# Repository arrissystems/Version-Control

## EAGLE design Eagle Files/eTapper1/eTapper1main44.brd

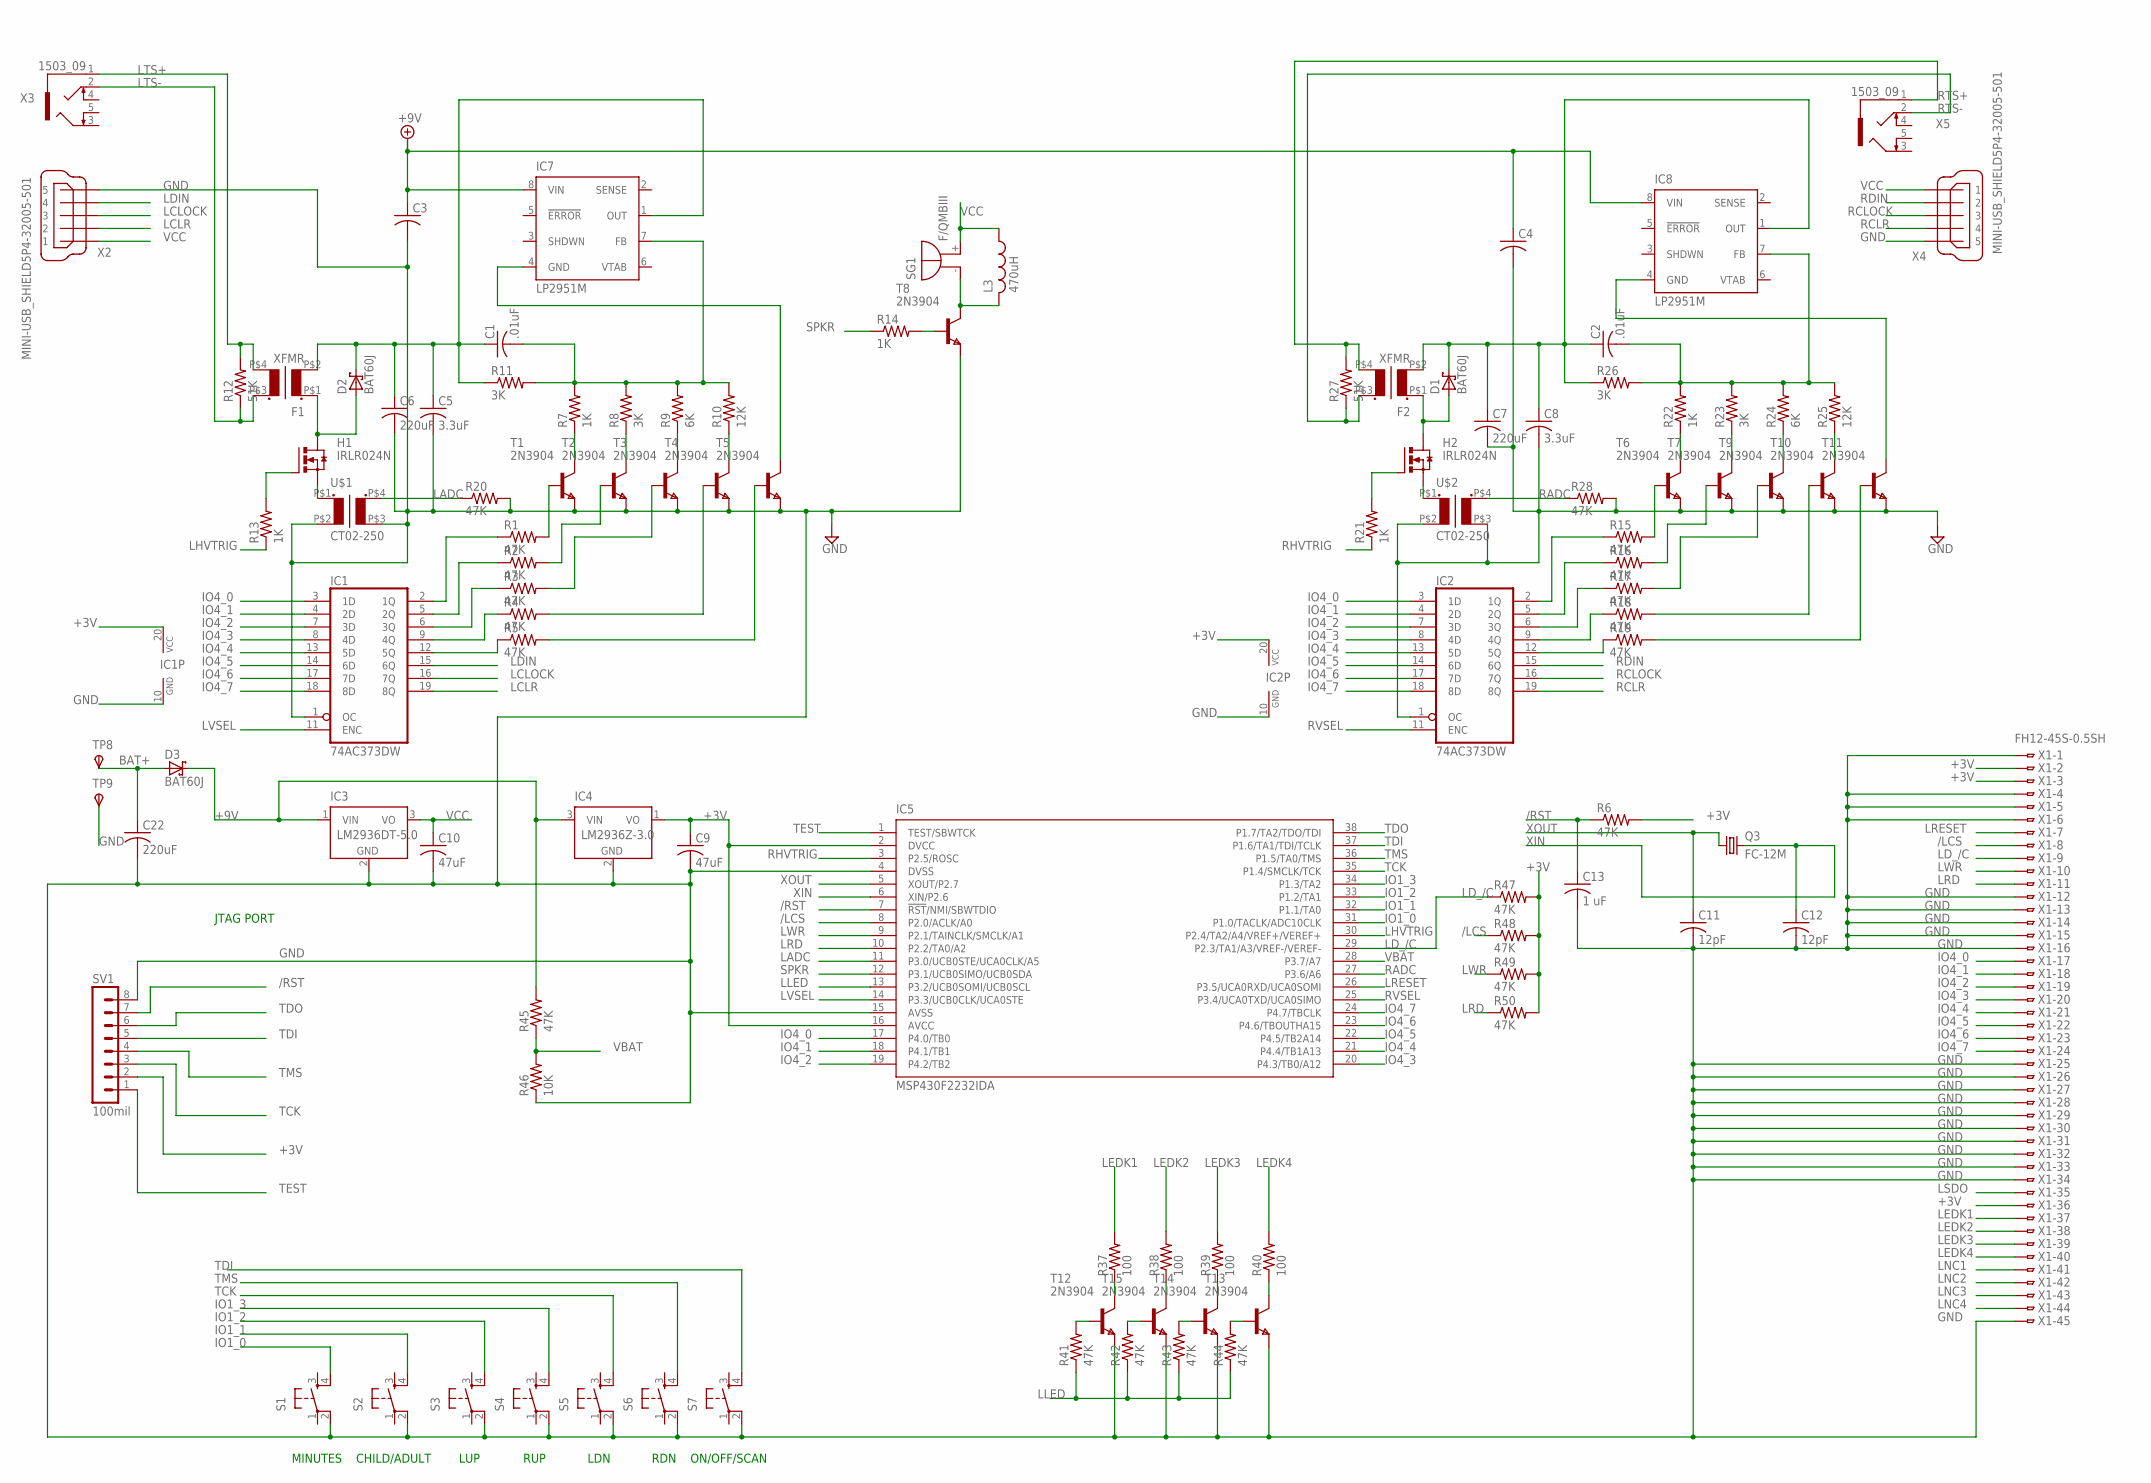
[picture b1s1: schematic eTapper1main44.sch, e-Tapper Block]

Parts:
C1, C2: .01uF; C0805
C3, C4: C-USC1206; C1206
C5, C8: 3.3uF; C0805
C6, C7, C22: 220uF; C1206
C9, C10: 47uF; C1206
C11, C12: 12pF; C0805
C13: 1 uF; C0805
D1, D2, D3: BAT60J; SOD323_ST
F1, F2: XFMR
H1, H2: IRLR024N; D-PAK_TO252AA
IC1, IC2: 74AC373DW; SO20W
IC3: LM2936DT-5.0; TO252
IC4: LM2936Z-3.0; TO92
IC5: MSP430F2232IDA; TSSOP38_R-PDSO-G38-DA
IC7, IC8: LP2951M; SO08
L3: 470uH; L2825P
Q3: FC-12M
R1, R2, R3, R4, R5, R6, R15, R16, R17, R18, R19, R20, R28, R41, R42, R43, R44, R45, R47, R48, R49, R50: 47K; R0402
R7, R13, R14, R21, R22: 1K; R0402
R8, R11, R23, R26: 3K; R0402
R9, R24: 6K; R0402
R10, R25: 12K; R0402
R12, R27: 51K; R0402
R37, R38, R39, R40: 100; R0402
R46: 10K; R0402
S1, S2, S3, S4, S5, S6, S7: 10-XX; B3F-10XX
SG1: F/QMBIII
SV1: 100mil; MA08-1
T1, T2, T3, T4, T5, T6, T7, T8, T9, T10, T11, T12, T13, T14, T15: 2N3904; SOT-23
TP8, TP9: TPSPAD1-20; P1-20
U$1, U$2: CT02-250
X1: FH12-45S-0.5SH
X2, X4: MINI-USB_SHIELD5P4-32005-501; 32005-501
X3, X5: 1503_09

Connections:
+3V: C9.1, IC1.20 (VCC), IC2.20 (VCC), IC4.1 (VO), IC5.2 (DVCC), IC5.16 (AVCC), R6.2, R47.2, R48.2, R49.2, R50.2, SV1.2, X1.2, X1.3, X1.36
+9V: C3.1, C4.1, D3.C, IC3.1 (VIN), IC4.3 (VIN), IC7.8 (VIN), IC8.8 (VIN), R45.2
/LCS: IC5.8 (P2.0/ACLK/A0), R48.1, X1.8
/RST: C13.1, IC5.7 (!RST!/NMI/SBWTDIO), R6.1, SV1.7
BAT+: C22.1, D3.A, TP8.TP
GND: C3.2, C4.2, C5.2, C6.2, C7.2, C8.2, C9.2, C10.2, C11.2, C12.2, C13.2, C22.2, IC1.1 (OC), IC1.10 (GND), IC2.1 (OC), IC2.10 (GND), IC3.2 (GND), IC4.2 (GND), IC5.4 (DVSS), IC5.15 (AVSS), R20.2, R28.2, R46.1, S1.2 (P1), S2.2 (P1), S3.2 (P1), S4.2 (P1), S5.2 (P1), S6.2 (P1), S7.2 (P1), SV1.8, T1.2 (E), T2.2 (E), T3.2 (E), T4.2 (E), T5.2 (E), T6.2 (E), T7.2 (E), T8.2 (E), T9.2 (E), T10.2 (E), T11.2 (E), T12.2 (E), T13.2 (E), T14.2 (E), T15.2 (E), TP9.TP, U$1.P$2 (P2), U$1.P$3 (S2), U$2.P$2 (P2), U$2.P$3 (S2), X1.1, X1.4, X1.5, X1.6, X1.12, X1.13, X1.14, X1.15, X1.16, X1.25, X1.26, X1.27, X1.28, X1.29, X1.30, X1.31, X1.32, X1.33, X1.34, X1.45, X2.5, X4.5
IO1_0: IC5.31 (P1.0/TACLK/ADC10CLK), S1.4 (S1)
IO1_1: IC5.32 (P1.1/TA0), S2.4 (S1)
IO1_2: IC5.33 (P1.2/TA1), S3.4 (S1)
IO1_3: IC5.34 (P1.3/TA2), S4.4 (S1)
IO4_0: IC1.3 (1D), IC2.3 (1D), IC5.17 (P4.0/TB0), X1.17
IO4_1: IC1.4 (2D), IC2.4 (2D), IC5.18 (P4.1/TB1), X1.18
IO4_2: IC1.7 (3D), IC2.7 (3D), IC5.19 (P4.2/TB2), X1.19
IO4_3: IC1.8 (4D), IC2.8 (4D), IC5.20 (P4.3/TB0/A12), X1.20
IO4_4: IC1.13 (5D), IC2.13 (5D), IC5.21 (P4.4/TB1A13), X1.21
IO4_5: IC1.14 (6D), IC2.14 (6D), IC5.22 (P4.5/TB2A14), X1.22
IO4_6: IC1.17 (7D), IC2.17 (7D), IC5.23 (P4.6/TBOUTHA15), X1.23
IO4_7: IC1.18 (8D), IC2.18 (8D), IC5.24 (P4.7/TBCLK), X1.24
LADC: IC5.11 (P3.0/UCB0STE/UCA0CLK/A5), R20.1, U$1.P$4 (S1)
LCLOCK: IC1.16 (7Q), X2.3
LCLR: IC1.19 (8Q), X2.2
LDIN: IC1.15 (6Q), X2.4
LD_/C: IC5.29 (P2.3/TA1/A3/VREF-/VEREF-), R47.1, X1.9
LEDK1: R37.2, X1.37
LEDK2: R38.2, X1.38
LEDK3: R39.2, X1.39
LEDK4: R40.2, X1.40
LHVTRIG: IC5.30 (P2.4/TA2/A4/VREF+/VEREF+), R13.1
LLED: IC5.13 (P3.2/UCB0SOMI/UCB0SCL), R41.1, R42.1, R43.1, R44.1
LNC1: X1.41
LNC2: X1.42
LNC3: X1.43
LNC4: X1.44
LRD: IC5.10 (P2.2/TA0/A2), R50.1, X1.11
LRESET: IC5.26 (P3.5/UCA0RXD/UCA0SOMI), X1.7
LSDO: X1.35
LTS+: F1.P$4 (S2), R12.2, X3.1
LTS-: F1.P$3 (S1), R12.1, X3.2
LVSEL: IC1.11 (ENC), IC5.14 (P3.3/UCB0CLK/UCA0STE)
LWR: IC5.9 (P2.1/TAINCLK/SMCLK/A1), R49.1, X1.10
unnamed: IC1.2 (1Q), R1.1
unnamed: IC1.5 (2Q), R2.1
unnamed: IC1.6 (3Q), R3.1
unnamed: IC1.9 (4Q), R4.1
unnamed: IC1.12 (5Q), R5.1
unnamed: L3.2, SG1.- (+), T8.1 (C)
unnamed: R4.2, T4.3 (B)
unnamed: R5.2, T5.3 (B)
unnamed: D2.A, F1.P$1 (P1), H1.4 (D)
unnamed: R7.1, T1.1 (C)
unnamed: R8.1, T2.1 (C)
unnamed: R9.1, T3.1 (C)
unnamed: R1.2, T1.3 (B)
unnamed: R2.2, T2.3 (B)
unnamed: R3.2, T3.3 (B)
unnamed: R10.1, T4.1 (C)
unnamed: C1.2, IC7.7 (FB), R7.2, R8.2, R9.2, R10.2, R11.2
unnamed: C1.1, C5.1, C6.1, D2.C, F1.P$2 (P2), IC7.1 (OUT), R11.1
unnamed: D1.A, F2.P$1 (P1), H2.4 (D)
unnamed: IC2.2 (1Q), R15.1
unnamed: H1.1 (G), R13.2
unnamed: R14.2, T8.3 (B)
unnamed: H1.3 (S), U$1.P$1 (P1)
unnamed: IC2.5 (2Q), R16.1
unnamed: IC2.6 (3Q), R17.1
unnamed: IC2.9 (4Q), R18.1
unnamed: IC2.12 (5Q), R19.1
unnamed: R44.2, T13.3 (B)
unnamed: R15.2, T6.3 (B)
unnamed: R16.2, T7.3 (B)
unnamed: R17.2, T9.3 (B)
unnamed: R18.2, T10.3 (B)
unnamed: R19.2, T11.3 (B)
unnamed: R22.1, T6.1 (C)
unnamed: R23.1, T7.1 (C)
unnamed: R24.1, T9.1 (C)
unnamed: R25.1, T10.1 (C)
unnamed: C2.2, IC8.7 (FB), R22.2, R23.2, R24.2, R25.2, R26.2
unnamed: C2.1, C7.1, C8.1, D1.C, F2.P$2 (P2), IC8.1 (OUT), R26.1
unnamed: R37.1, T12.1 (C)
unnamed: H2.1 (G), R21.2
unnamed: R38.1, T15.1 (C)
unnamed: R39.1, T14.1 (C)
unnamed: IC7.4 (GND), T5.1 (C)
unnamed: R40.1, T13.1 (C)
unnamed: IC8.4 (GND), T11.1 (C)
unnamed: R43.2, T14.3 (B)
unnamed: R41.2, T12.3 (B)
unnamed: R42.2, T15.3 (B)
unnamed: H2.3 (S), U$2.P$1 (P1)
RADC: IC5.27 (P3.6/A6), R28.1, U$2.P$4 (S1)
RCLOCK: IC2.16 (7Q), X4.3
RCLR: IC2.19 (8Q), X4.4
RDIN: IC2.15 (6Q), X4.2
RHVTRIG: IC5.3 (P2.5/ROSC), R21.1
RTS+: F2.P$4 (S2), R27.2, X5.1
RTS-: F2.P$3 (S1), R27.1, X5.2
RVSEL: IC2.11 (ENC), IC5.25 (P3.4/UCA0TXD/UCA0SIMO)
SPKR: IC5.12 (P3.1/UCB0SIMO/UCB0SDA), R14.1
TCK: IC5.35 (P1.4/SMCLK/TCK), S5.4 (S1), SV1.3
TDI: IC5.37 (P1.6/TA1/TDI/TCLK), S7.4 (S1), SV1.5
TDO: IC5.38 (P1.7/TA2/TDO/TDI), SV1.6
TEST: IC5.1 (TEST/SBWTCK), SV1.1
TMS: IC5.36 (P1.5/TA0/TMS), S6.4 (S1), SV1.4
VBAT: IC5.28 (P3.7/A7), R45.1, R46.2
VCC: C10.1, IC3.3 (VO), L3.1, SG1.+ (-), X2.1, X4.1
XIN: C12.1, IC5.6 (XIN/P2.6), Q3.2
XOUT: C11.1, IC5.5 (XOUT/P2.7), Q3.1

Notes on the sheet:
ON/OFF/SCAN
MINUTES
CHILD/ADULT
LUP
RUP
JTAG PORT
LDN
RDN

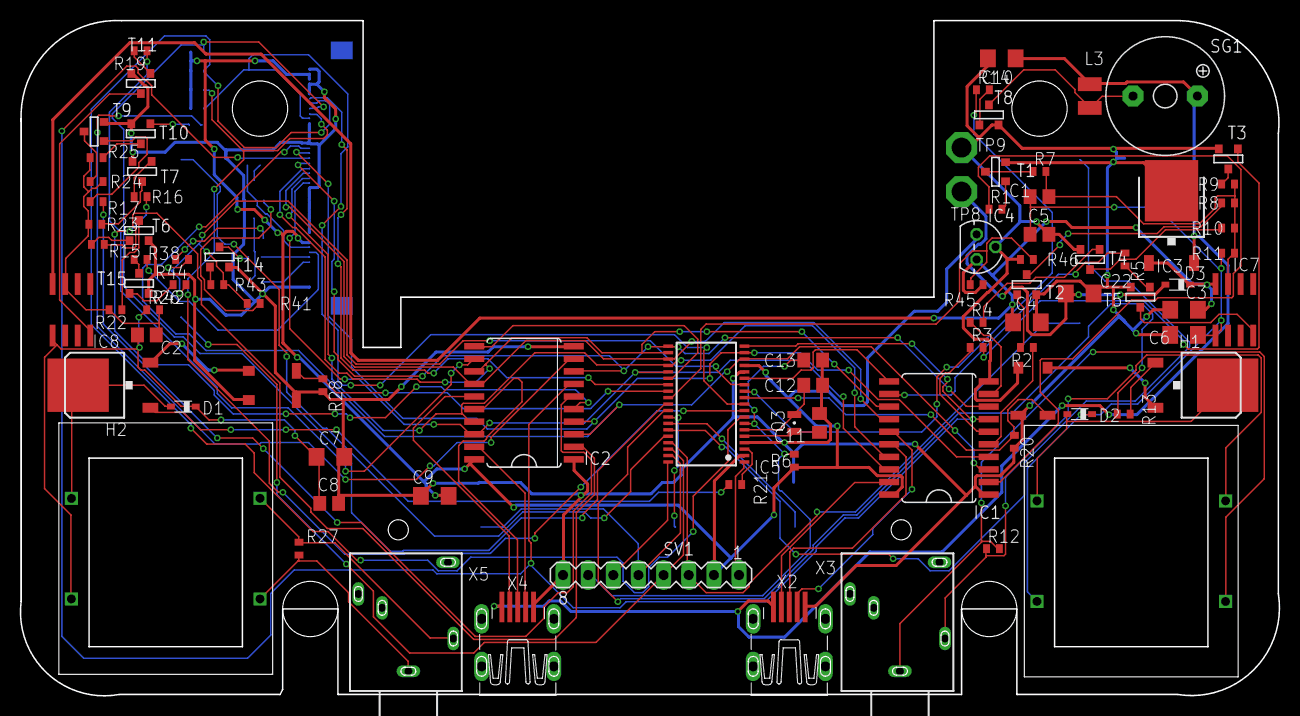
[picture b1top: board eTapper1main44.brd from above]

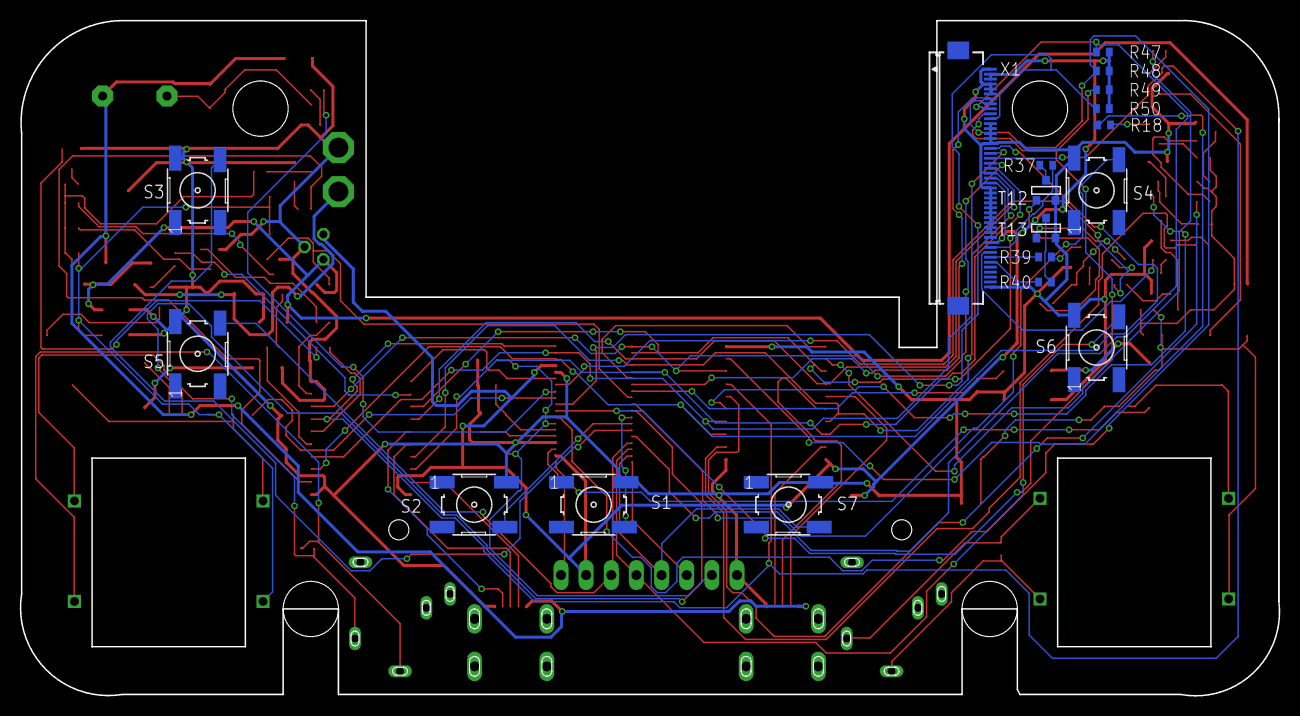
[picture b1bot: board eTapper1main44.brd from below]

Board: 2 copper layers, 127.2 x 68.2 mm, 105 parts (18 on the bottom side), 103 nets.

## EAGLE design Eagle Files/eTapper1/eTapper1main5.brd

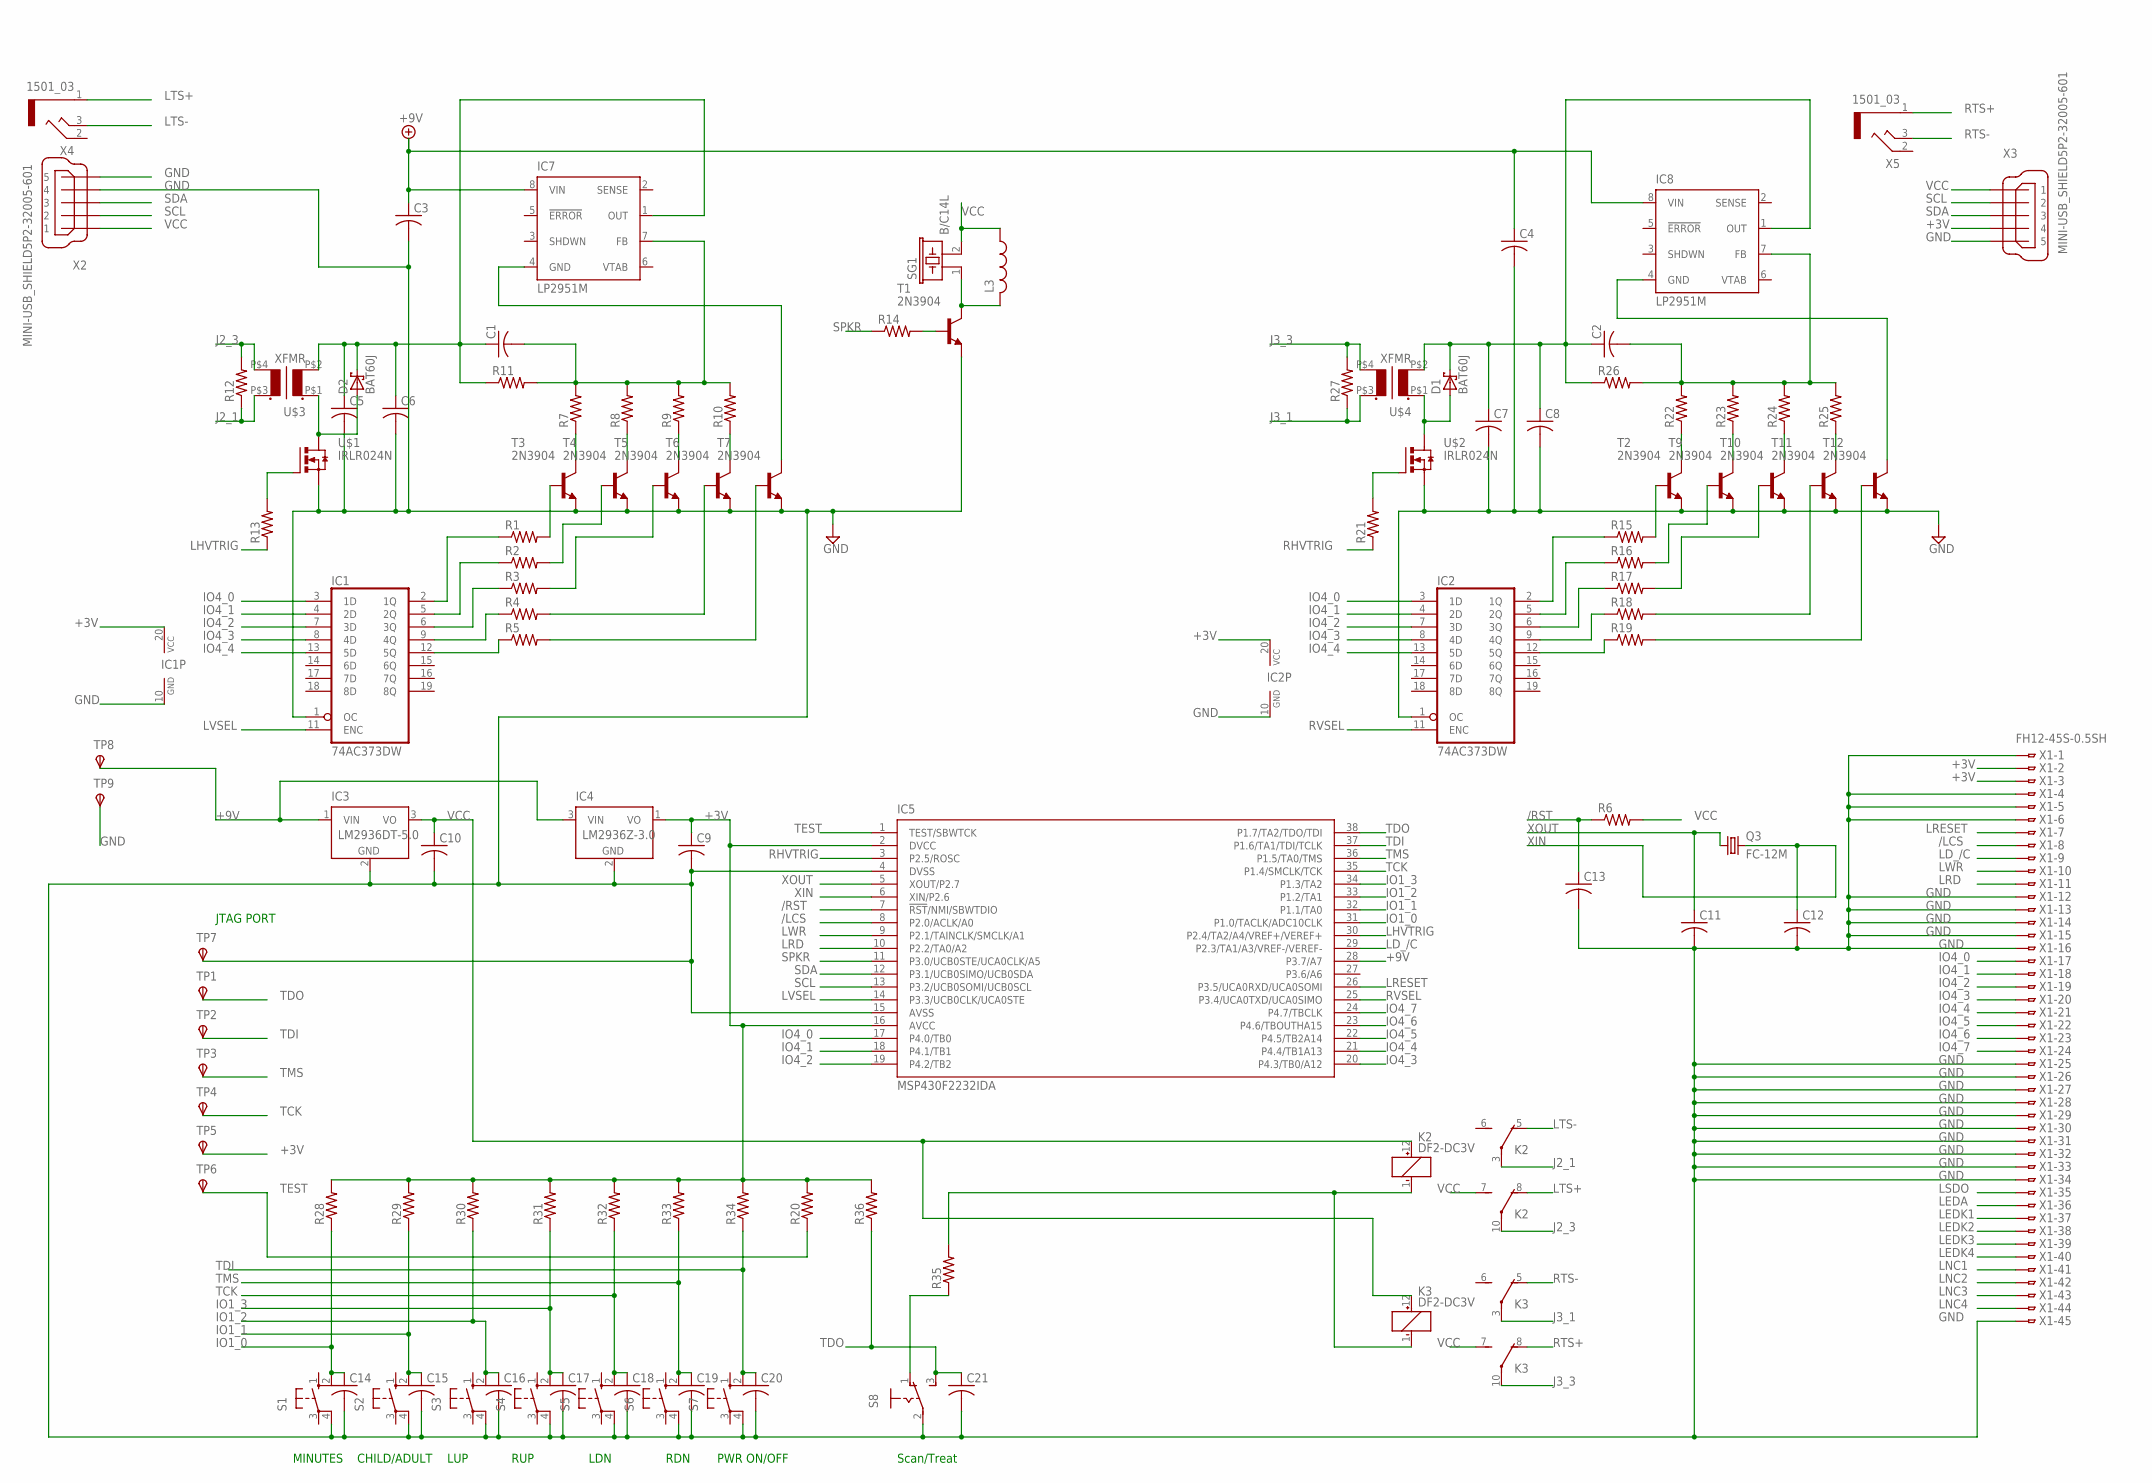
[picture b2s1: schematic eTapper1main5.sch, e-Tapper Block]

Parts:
C1, C2, C3, C4, C5, C6, C7, C8, C9, C10, C11, C12, C13, C14, C15, C16, C17, C18, C19, C20, C21: C-USC0805; C0805
D1, D2: BAT60J; SOD323_ST
IC1, IC2: 74AC373DW; SO20W
IC3: LM2936DT-5.0; TO252
IC4: LM2936Z-3.0; TO92
IC5: MSP430F2232IDA; TSSOP38_R-PDSO-G38-DA
IC7, IC8: LP2951M; SO08
K2, K3: DF2-DC3V; DF2
L3: L-USL2825P; L2825P
Q3: FC-12M
R1, R2, R3, R4, R5, R6, R7, R8, R9, R10, R11, R12, R13, R14, R15, R16, R17, R18, R19, R20, R21, R22, R23, R24, R25, R26, R27, R28, R29, R30, R31, R32, R33, R34, R35, R36: R-US_R0402; R0402
S1, S2, S3, S4, S5, S6, S7: 10-XX; B3F-10XX
S8: M251
SG1: B/C14L
T1, T2, T3, T4, T5, T6, T7, T9, T10, T11, T12: 2N3904; TO92
TP1, TP2, TP3, TP4, TP5, TP6, TP7, TP8, TP9: TPSTP06R; TP06R
U$1, U$2: IRLR024N; I-PAK_TO251AA
U$3, U$4: XFMR
X1: FH12-45S-0.5SH
X2, X3: MINI-USB_SHIELD5P2-32005-601; 32005-601
X4, X5: 1501_03

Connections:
+3V: C9.1, IC1.20 (VCC), IC2.20 (VCC), IC4.1 (VO), IC5.2 (DVCC), IC5.16 (AVCC), R20.2, R28.2, R29.2, R30.2, R31.2, R32.2, R33.2, R34.2, R36.2, TP5.TP, X1.2, X1.3, X3.4
+9V: C3.1, C4.1, IC3.1 (VIN), IC4.3 (VIN), IC5.28 (P3.7/A7), IC7.8 (VIN), IC8.8 (VIN), TP8.TP
/LCS: IC5.8 (P2.0/ACLK/A0), X1.8
/RST: C13.1, IC5.7 (!RST!/NMI/SBWTDIO), R6.1
GND: C3.2, C4.2, C5.2, C6.2, C7.2, C8.2, C9.2, C10.2, C11.2, C12.2, C13.2, C14.2, C15.2, C16.2, C17.2, C18.2, C19.2, C20.2, C21.2, IC1.1 (OC), IC1.10 (GND), IC2.1 (OC), IC2.10 (GND), IC3.2 (GND), IC4.2 (GND), IC5.4 (DVSS), IC5.15 (AVSS), S1.4 (P1), S2.4 (P1), S3.4 (P1), S4.4 (P1), S5.4 (P1), S6.4 (P1), S7.4 (P1), S8.2, T1.3 (E), T2.3 (E), T3.3 (E), T4.3 (E), T5.3 (E), T6.3 (E), T7.3 (E), T9.3 (E), T10.3 (E), T11.3 (E), T12.3 (E), TP7.TP, TP9.TP, U$1.3 (S), U$2.3 (S), X1.1, X1.4, X1.5, X1.6, X1.12, X1.13, X1.14, X1.15, X1.16, X1.25, X1.26, X1.27, X1.28, X1.29, X1.30, X1.31, X1.32, X1.33, X1.34, X1.45, X2.4, X2.5, X3.5
IO1_0: C14.1, IC5.31 (P1.0/TACLK/ADC10CLK), R28.1, S1.2 (S1)
IO1_1: C15.1, IC5.32 (P1.1/TA0), R29.1, S2.2 (S1)
IO1_2: C16.1, IC5.33 (P1.2/TA1), R30.1, S3.2 (S1)
IO1_3: C17.1, IC5.34 (P1.3/TA2), R31.1, S4.2 (S1)
IO4_0: IC1.3 (1D), IC2.3 (1D), IC5.17 (P4.0/TB0), X1.17
IO4_1: IC1.4 (2D), IC2.4 (2D), IC5.18 (P4.1/TB1), X1.18
IO4_2: IC1.7 (3D), IC2.7 (3D), IC5.19 (P4.2/TB2), X1.19
IO4_3: IC1.8 (4D), IC2.8 (4D), IC5.20 (P4.3/TB0/A12), X1.20
IO4_4: IC1.13 (5D), IC2.13 (5D), IC5.21 (P4.4/TB1A13), X1.21
IO4_5: IC5.22 (P4.5/TB2A14), X1.22
IO4_6: IC5.23 (P4.6/TBOUTHA15), X1.23
IO4_7: IC5.24 (P4.7/TBCLK), X1.24
J2_1: K2.3, R12.1, U$3.P$3 (S1)
J2_3: K2.10, R12.2, U$3.P$4 (S2)
J3_1: K3.3, R27.1, U$4.P$3 (S1)
J3_3: K3.10, R27.2, U$4.P$4 (S2)
LD_/C: IC5.29 (P2.3/TA1/A3/VREF-/VEREF-), X1.9
LEDA: X1.36
LEDK1: X1.37
LEDK2: X1.38
LEDK3: X1.39
LEDK4: X1.40
LHVTRIG: IC5.30 (P2.4/TA2/A4/VREF+/VEREF+), R13.1
LNC1: X1.41
LNC2: X1.42
LNC3: X1.43
LNC4: X1.44
LRD: IC5.10 (P2.2/TA0/A2), X1.11
LRESET: IC5.26 (P3.5/UCA0RXD/UCA0SOMI), X1.7
LSDO: X1.35
LTS+: K2.8 (O), X4.1
LTS-: K2.5 (O), X4.3
LVSEL: IC1.11 (ENC), IC5.14 (P3.3/UCB0CLK/UCA0STE)
LWR: IC5.9 (P2.1/TAINCLK/SMCLK/A1), X1.10
unnamed: IC1.2 (1Q), R1.1
unnamed: IC1.5 (2Q), R2.1
unnamed: IC1.6 (3Q), R3.1
unnamed: IC1.9 (4Q), R4.1
unnamed: IC1.12 (5Q), R5.1
unnamed: L3.2, SG1.1, T1.1 (C)
unnamed: R4.2, T6.2 (B)
unnamed: R5.2, T7.2 (B)
unnamed: D2.A, U$1.2 (D), U$1.4 (D), U$3.P$1 (P1)
unnamed: R7.1, T3.1 (C)
unnamed: R8.1, T4.1 (C)
unnamed: R9.1, T5.1 (C)
unnamed: R1.2, T3.2 (B)
unnamed: R2.2, T4.2 (B)
unnamed: R3.2, T5.2 (B)
unnamed: R10.1, T6.1 (C)
unnamed: C1.2, IC7.7 (FB), R7.2, R8.2, R9.2, R10.2, R11.2
unnamed: C1.1, C5.1, C6.1, D2.C, IC7.1 (OUT), R11.1, U$3.P$2 (P2)
unnamed: D1.A, U$2.2 (D), U$2.4 (D), U$4.P$1 (P1)
unnamed: IC2.2 (1Q), R15.1
unnamed: R13.2, U$1.1 (G)
unnamed: R14.2, T1.2 (B)
unnamed: R35.1, S8.1 (O)
unnamed: IC2.5 (2Q), R16.1
unnamed: IC2.6 (3Q), R17.1
unnamed: IC2.9 (4Q), R18.1
unnamed: IC2.12 (5Q), R19.1
unnamed: R15.2, T2.2 (B)
unnamed: R16.2, T9.2 (B)
unnamed: R17.2, T10.2 (B)
unnamed: R18.2, T11.2 (B)
unnamed: R19.2, T12.2 (B)
unnamed: K2.1 (-), K3.1 (-), R35.2
unnamed: R22.1, T2.1 (C)
unnamed: R23.1, T9.1 (C)
unnamed: R24.1, T10.1 (C)
unnamed: R25.1, T11.1 (C)
unnamed: C2.2, IC8.7 (FB), R22.2, R23.2, R24.2, R25.2, R26.2
unnamed: C2.1, C7.1, C8.1, D1.C, IC8.1 (OUT), R26.1, U$4.P$2 (P2)
unnamed: R21.2, U$2.1 (G)
unnamed: IC7.4 (GND), T7.1 (C)
unnamed: IC8.4 (GND), T12.1 (C)
RHVTRIG: IC5.3 (P2.5/ROSC), R21.1
RTS+: K3.8 (O), X5.1
RTS-: K3.5 (O), X5.3
RVSEL: IC2.11 (ENC), IC5.25 (P3.4/UCA0TXD/UCA0SIMO)
SCL: IC5.13 (P3.2/UCB0SOMI/UCB0SCL), X2.2, X3.2
SDA: IC5.12 (P3.1/UCB0SIMO/UCB0SDA), X2.3, X3.3
SPKR: IC5.11 (P3.0/UCB0STE/UCA0CLK/A5), R14.1
TCK: C18.1, IC5.35 (P1.4/SMCLK/TCK), R32.1, S5.2 (S1), TP4.TP
TDI: C20.1, IC5.37 (P1.6/TA1/TDI/TCLK), R34.1, S7.2 (S1), TP2.TP
TDO: C21.1, IC5.38 (P1.7/TA2/TDO/TDI), R36.1, S8.3 (S), TP1.TP
TEST: IC5.1 (TEST/SBWTCK), R20.1, TP6.TP
TMS: C19.1, IC5.36 (P1.5/TA0/TMS), R33.1, S6.2 (S1), TP3.TP
VCC: C10.1, IC3.3 (VO), K2.7 (S), K2.12 (+), K3.7 (S), K3.12 (+), L3.1, R6.2, SG1.2, X2.1, X3.1
XIN: C12.1, IC5.6 (XIN/P2.6), Q3.2
XOUT: C11.1, IC5.5 (XOUT/P2.7), Q3.1

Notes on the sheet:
PWR ON/OFF
Scan/Treat
MINUTES
CHILD/ADULT
LUP
RUP
JTAG PORT
LDN
RDN

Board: 2 copper layers, 108 parts (8 on the bottom side), 86 nets, no tracks yet.
